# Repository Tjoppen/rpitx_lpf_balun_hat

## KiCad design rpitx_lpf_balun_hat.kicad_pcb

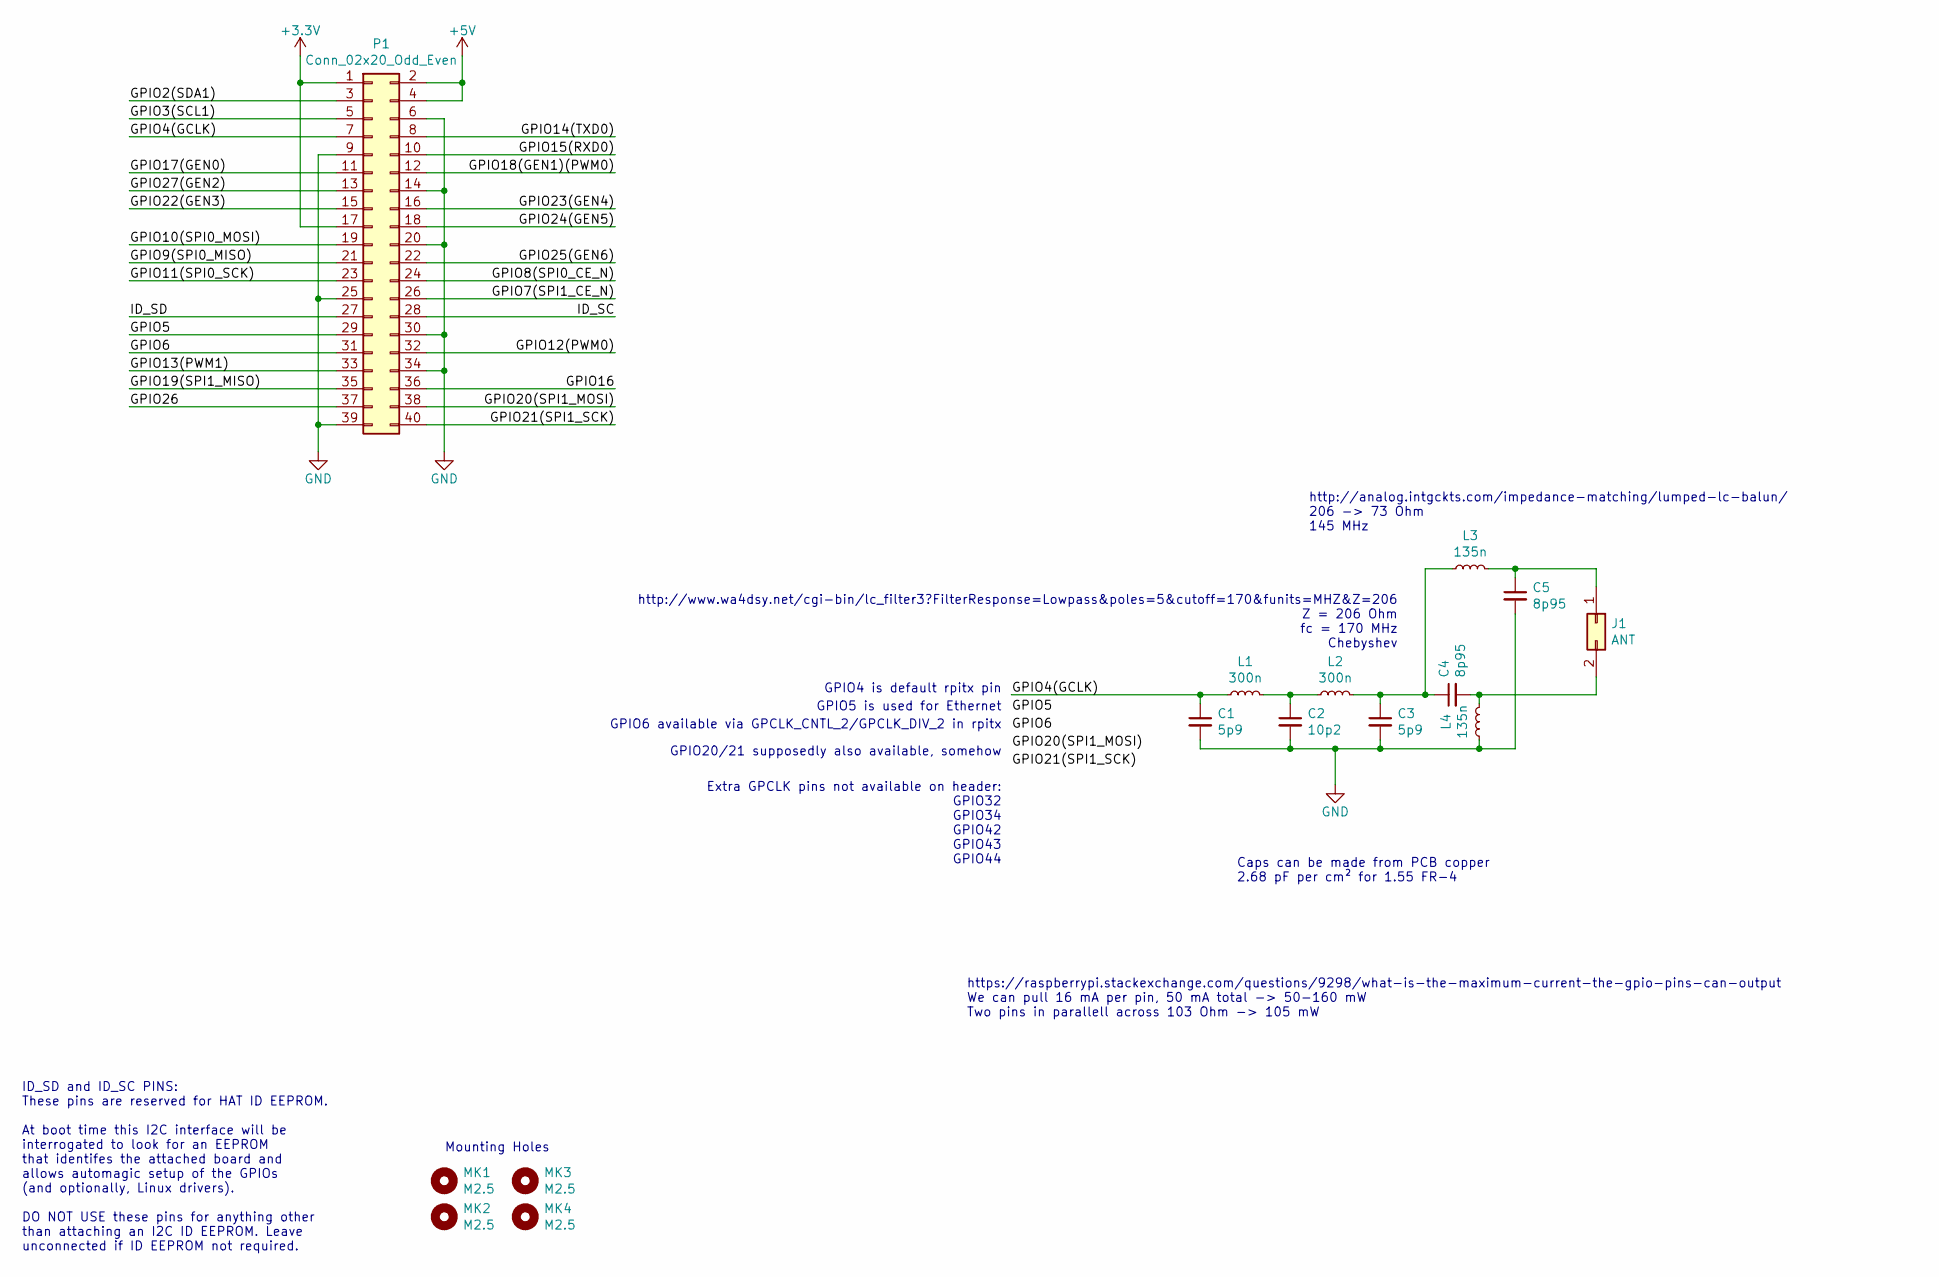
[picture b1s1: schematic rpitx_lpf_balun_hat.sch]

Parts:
C1, C3: 5p9; C_0805_2012Metric
C2: 10p2; C_0805_2012Metric
C4, C5: 8p95; C_0805_2012Metric
J1: ANT; rpitx_ant
L1, L2: 300n; L_0805_2012Metric
L3, L4: 135n; L_0805_2012Metric
MK1, MK2, MK3, MK4: M2.5; MountingHole_2.7mm_M2.5
P1: Conn_02x20_Odd_Even; PinSocket_2x20_P2.54mm_Vertical

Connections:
+3V3: P1.1, P1.17
+5V: P1.2, P1.4
/GPIO2(SDA1): P1.3
/GPIO3(SCL1): P1.5
/GPIO4(GCLK): C1.1, L1.1, P1.7
/GPIO5: P1.29
/GPIO6: P1.31
/GPIO7(SPI1_CE_N): P1.26
/GPIO8(SPI0_CE_N): P1.24
/GPIO9(SPI0_MISO): P1.21
/GPIO10(SPI0_MOSI): P1.19
/GPIO11(SPI0_SCK): P1.23
/GPIO12(PWM0): P1.32
/GPIO13(PWM1): P1.33
/GPIO14(TXD0): P1.8
/GPIO15(RXD0): P1.10
/GPIO16: P1.36
/GPIO17(GEN0): P1.11
/GPIO18(GEN1)(PWM0): P1.12
/GPIO19(SPI1_MISO): P1.35
/GPIO20(SPI1_MOSI): P1.38
/GPIO21(SPI1_SCK): P1.40
/GPIO22(GEN3): P1.15
/GPIO23(GEN4): P1.16
/GPIO24(GEN5): P1.18
/GPIO25(GEN6): P1.22
/GPIO26: P1.37
/GPIO27(GEN2): P1.13
/ID_SC: P1.28
/ID_SD: P1.27
GND: C1.2, C2.2, C3.2, C5.2, L4.1, P1.6, P1.9, P1.14, P1.20, P1.25, P1.30, P1.34, P1.39
unnamed: C2.1, L1.2, L2.1
unnamed: C3.1, C4.1, L2.2, L3.1
unnamed: C4.2, J1.2, L4.2
unnamed: C5.1, J1.1, L3.2

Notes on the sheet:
ID_SD and ID_SC PINS: These pins are reserved for HAT ID EEPROM. At boot time this I2C interface will be interrogated to look for an EEPROM that identifes the attached board and allows automagic setup of the GPIOs (and optionally, Linux drivers). DO NOT USE these pins for anything other than attach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
Mounting Holes
Extra GPCLK pins not available on header: GPIO32 GPIO34 GPIO42 GPIO43 GPIO44
GPIO6 available via GPCLK_CNTL_2/GPCLK_DIV_2 in rpitx
GPIO5 is used for Ethernet
GPIO4 is default rpitx pin
GPIO20/21 supposedly also available, somehow
https://raspberrypi.stackexchange.com/questions/9298/what-is-the-maximum-current-the-gpio-pins-can-output We can pull 16 mA per pin, 50 mA total -> 50-160 mW Two pins in parallell across 103 Ohm -> 105 mW
http://www.wa4dsy.net/cgi-bin/lc_filter3?FilterResponse=Lowpass&poles=5&cutoff=170&funits=MHZ&Z=206 Z = 206 Ohm fc = 170 MHz Chebyshev
http://analog.intgckts.com/impedance-matching/lumped-lc-balun/ 206 -> 73 Ohm 145 MHz
Caps can be made from PCB copper 2.68 pF per cm² for 1.55 FR-4

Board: 2 copper layers, 15 parts (1 on the bottom side), 8 nets, no tracks yet.

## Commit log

2019-02-14 Blank template
2019-02-14 Port to 5.0.2
    Why the templates aren't ported already I don't know
2019-02-14 5th order Chebyshev low-pass + balun
2019-02-14 Add second 206 Ohm path
    This way we don't have to mess around with rpitx to get GPIO6 output
2019-02-14 Only 206 Ohm circuit, add thing to solder antenna to
2019-02-14 Hook footprint lib up
2019-02-14 Rough placement
